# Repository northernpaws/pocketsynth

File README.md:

# Pocket Synth

[Online Board & Schematic View](https://kicanvas.org/?github=https%3A%2F%2Fgithub.com%2Fnorthernpaws%2Fpocketsynth%2Fblob%2Fmain%2Fhardware%2Fdevice%2Fpocket_synth.kicad_pro)

This repository contains my project for an STM32H7-based sequencer, synthesizer, and sampler, all in a small phone-sized pocketable form factor. 

  * 480 MHz Arm® Cortex®-M7 32-bit Processor (`STM32H743ZIT6`)
    * Floating-point unit
    * DSP instructions
    * High-speed memory controller
    * Quad SPI interface for flash
    * High-speed USB host and device mode
    * Several SAI audio blocks
  * 2.4" 240x320 TFT IPS Display (`ER-TFT024IPS-3`)
    * Capacitive touch
  * 24 bit Audio Codec (`NAU88C22YG`)
    * DAC: 94dB SNR and -84dB THD (“A” weighted)
    * ADC: 90dB SNR and -80dB THD (“A” weighted)
    * Integrated BTL speaker driver: 1W into 8Ω
    * Integrated head-phone driver: 40mW into 16Ω
  * Optional Bluetooth Classic and BLE Audio Source (`FSC-BT6038`)
    * Wirelessly connect Bluethooth headphones and speakers
    * Supports various high-fedality audio protocols
    * Note: Audio transmitter does not support other BLE protocols, such as MIDI
  * Optional Wifi and BLE capabilities (`ESP32-C3-MINI-1`)
    * Wifi sample management and transfer
    * BLE MIDI
  * Interal speaker
  * Internal microphone
  * SDRAM for sample pool and audio processing
    * Part allocated to in-memory sample pool for project
    * Part allocated to audio effects processing
    * Variable sizes in similar footprint available, up to 512Mbit:
        * 16bit * 48000Hz = 768,000b/s = 0.768Mb/s
        * 128Mb / 0.768Mb/s = 166.66 seconds of mono audio (`IS42S16800J-7TL`)
        * 256Mb / 0.768Mb/s = 333.33 seconds of mono audio (`IS42S16160J-7TLI`)
        * 512Mb / 0.768Mb/s = 666.66 seconds of mono audio (`IS42S16320F-7TLI`)
  * Micro SD Card
    * Saving and loading projects
      * Transfer and back up projects to a computer
    * Saving and loading samples
      * Load samples from a computer
      * Save samples recorded on the device
  * 3.3v NOR Flash (`MT25QUxxxxxx1xW7` 256M/128M/64M)
    * Stores device settings
    * Small storage space for projects and samples without SD card
    * Provides storage for cross-SD card samples
  * USB-C
    * USB-PD fast charging
    * Possible future audio interface mode
  * MIDI in/out via TRS minijack
  * 16 Multi-Purpose primary keys
    * Hot-swappable Kalih Choc keyswitches (V1 and V2 compatible)
    * RGB LEDs for state indicators
  * Accelerometer and Gyroscope (`LSM6DS3`)
    * Can be used as sequencer parameters
    * Can be recorded for automation inputs
    * Used for auto sleep/wake
  * USB-PD Battery Charge Controller (`MAX77789` or `MAX77757`)
    * 3A fast-charge current
    * 13.4V input voltage
    * Detection for legacy SDP, DCP, and CDP chargers
  * Two-Button Smart Reset (`STM6510`)
    * Hold two input buttons to power off the device if it freezes and power gets latched on

## Step Sequencer

The step sequencer on the device is modeled after popular semantics used by hardware sequencers, such as the Elektron Digitone and Digitakt, OP-1, OP-Z, Pocket Operators, Woovebox, etc.

> The hard requirements of the step sequencer and audio engine are not defined yet because they are under active development.

  * As many projects as the SD card or internal memory can store
    * 128 Patterns (TBD)
      * 8-16 Audio or MIDI tracks per pattern (TBD)
    * 8-24 Songs (arrangements of patterns) (TBD)
  * 8-16 voice polyphony (TBD)
    * 2-3 LFO per voice (TBD)

## Audio

The primary audio engine chain runs at 16bit 44.1Khz, but supports stereo audio effects. 16 bit audio was selected as it had suitable depth without being too large for a small embedded device to reasonably process. 44.1Khz also has a good frequency range, and has been the standard for CDs and many music streaming platforms for a long time.

### Sampling

The sampling engine runs 16bit 44.1Khz and saves and loads samples in single-channel mono.

Samples recoded from the internal or external mic are sampled at 24 bits into the device's SDRAM to provide a decent noise floor, and then filtered and downsampled to 16 bits for saving after they've been edited by the user.

The 16bit @ 44.1Khz sampling parameters provdes a good balance between audio quality, and reasonable utilization of the SDRAM without needing extremely large and expensive SDRAM chips:

```
16bit * 48000Hz = 768,000b/s = 0.768Mb/s
128Mb / 0.768Mb/s = 166.66 seconds of mono audio
256Mb / 0.768Mb/s = 333.33 seconds of mono audio
512Mb / 0.768Mb/s = 666.66 seconds of mono audio
```

> Note that some of the space calculated above (actual amount will be configurable) is allocated to the audio effects processing chain, i.e. for reverb and delay. 

## Attribution

### 3D Models

Majority of 3D models for PCB components are from their respective manufactures, with the exception of:

  - https://grabcad.com/library/kailh-low-profile-mechanical-keyboard-switch-1
  - https://grabcad.com/library/kailh-low-profile-keycaps-1
  - https://cad.grabcad.com/library/sk6812mini-e-led-1

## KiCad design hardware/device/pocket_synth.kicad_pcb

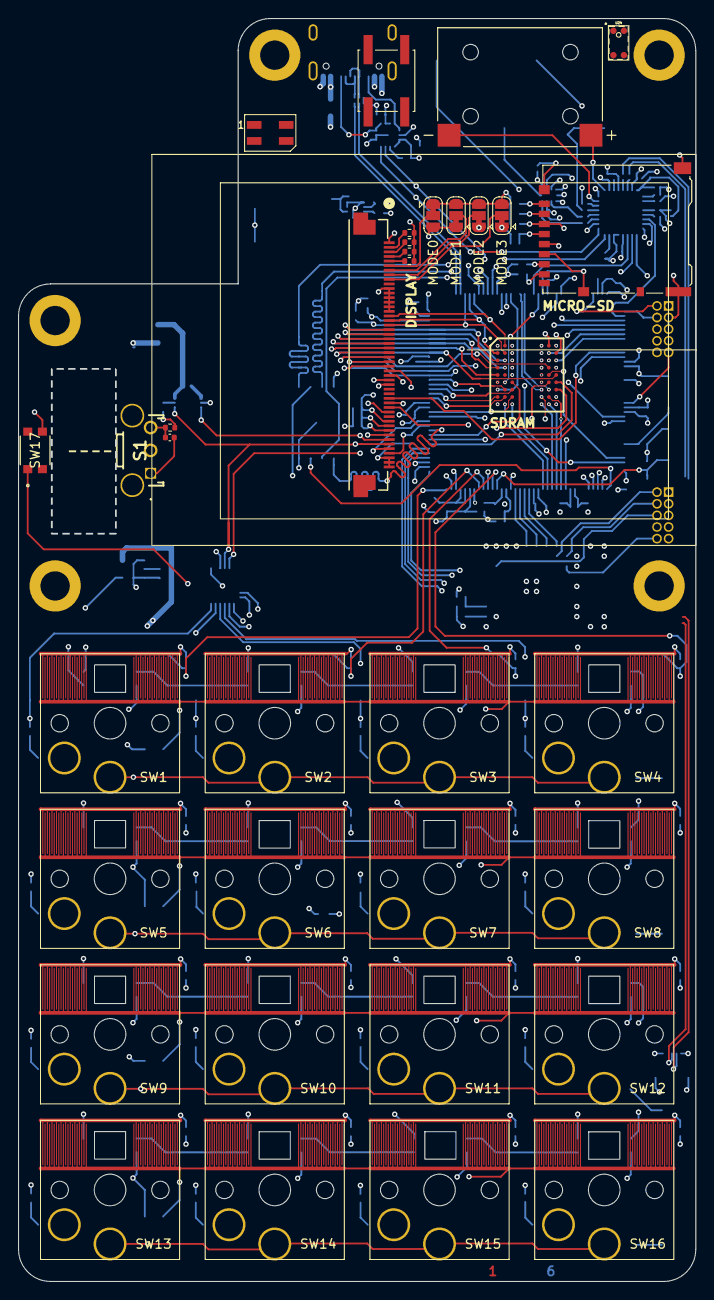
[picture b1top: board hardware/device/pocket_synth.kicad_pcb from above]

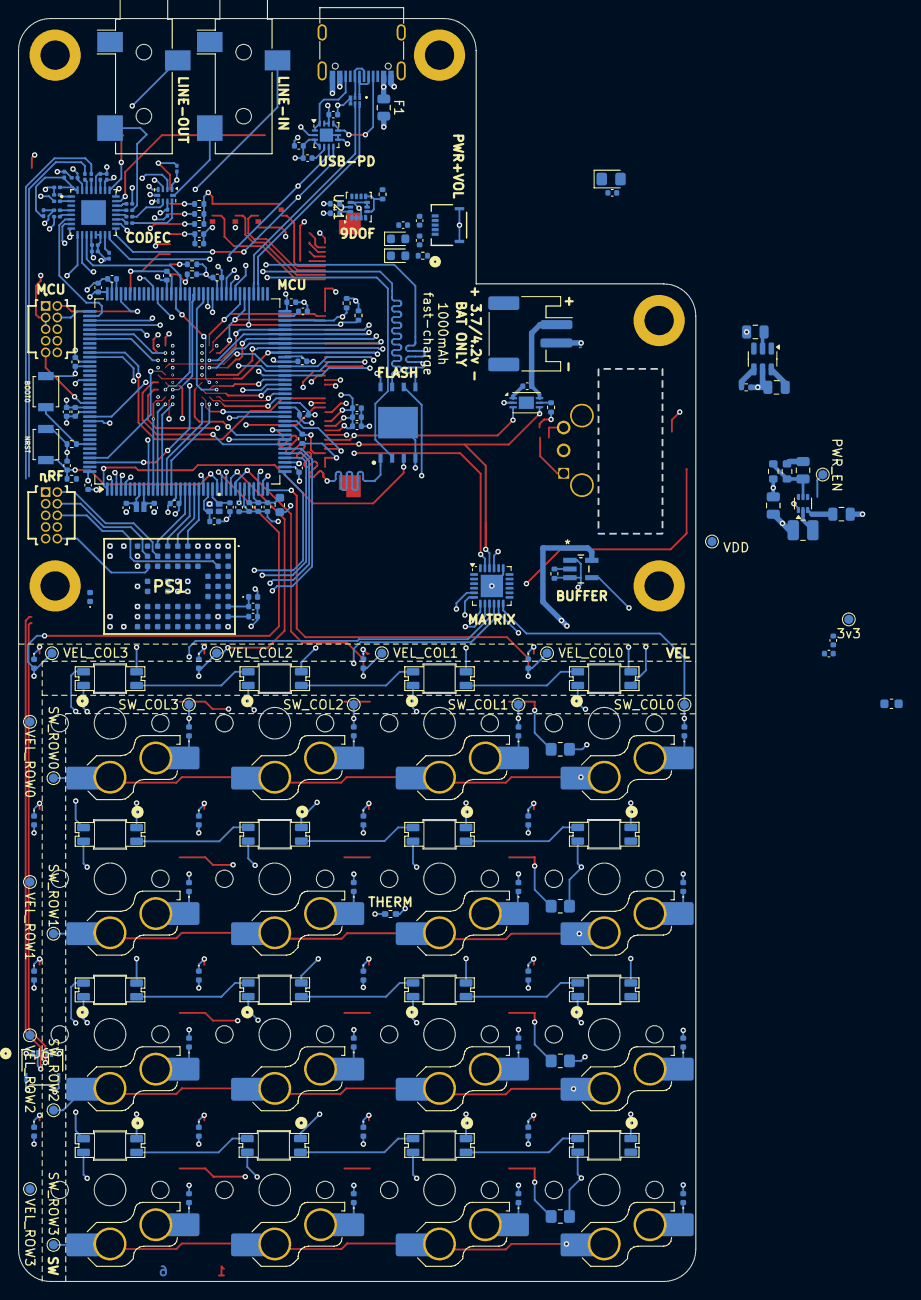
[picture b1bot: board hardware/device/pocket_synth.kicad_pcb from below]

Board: 6 copper layers, 74.0 x 138.0 mm, 231 parts (175 on the bottom side), 221 nets.

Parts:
BT1: Battery; JST_PH_S2B-PH-SM4-TB_1x02-1MP_P2.00mm_Horizontal
C1, C2: 2.2 µF; C_0402_1005Metric
C3: 1 µF; C_0402_1005Metric
C4, C5: 9pF; C_0402_1005Metric
C6, C14: 4.3pF; C_0402_1005Metric
C7: 0.1uF; C_0201_0603Metric
C8, C17, C21, C24: 0.1uF; C_0402_1005Metric
C9: 4.7uF; C_0805_2012Metric
C10, C11: 22uF; C_0402_1005Metric
C12: 22uF; C_0805_2012Metric
C13: 120pF; C_0805_2012Metric
C15, C16: 4.7uF; C_0402_1005Metric
C18: 1uF; C_0402_1005Metric
C19, C20: 1uF; C_0805_2012Metric
C22, C25: 10uF; C_0402_1005Metric
C26: 0.1uF; C_0603_1608Metric
C27, C29, C30, C31, C52, C53: 4.7uF; C_0201_0603Metric
C32, C33, C34, C35, C38, C42, C47, C51: 1uF; C_0201_0603Metric
C36, C37: 220uF; C_0201_0603Metric
C58: 10uf; C_0402_1005Metric
C59, C60, C61, C82, C83, C84, C85, C86, C87, C91, C92: 100nf; C_0402_1005Metric
C81: 0.1uf; C_0402_1005Metric
C88: 10nf; C_0402_1005Metric
C89, C90: 1uf; C_0402_1005Metric
D1, D2, D3, D4, D5, D6, D7, D8, D9, D10, D11, D12, D13, D14, D15, D16, D21, D22, D23, D24, D25, D26, D27, D28, D29, D30, D31, D32, D33, D34, D35, D36, D37, D38: D; D_0402_1005Metric
D17: 3v3_PWR; LED_0805_2012Metric_Pad1.15x1.40mm_HandSolder
D18, D19: D; D_0603_1608Metric
D20: METRONOME; LED_SK6812MINI_PLCC4_3.5x3.5mm_P1.75mm
F1: Fuse; Fuse_0805_2012Metric
FB9: 120r; L_0603_1608Metric
H1, H2, H3, H4, H5: M3; MountingHole_3.2mm_M3_DIN965_Pad
IC1: W25Q512JVEIQ
IC2: IS42S16160J-7BLI
IC3: SP3401-02UTG; SP340102UTG
J1: POT_CONN; CONN_503480-0540_MOL
J2: USB; USB_C_Receptacle_G-Switch_GT-USB-7010ASV
J3: MICRO_SD; microSD_HC_Hirose_DM3AT-SF-PEJM5
J6: HP; CONN_503480-0540_MOL
J8: LINE_OUT; Jack_3.5mm_CUI_SJ-3523-SMT_Horizontal
J9: LINE_IN; Jack_3.5mm_CUI_SJ-3523-SMT_Horizontal
JP1: MODE0; SolderJumper-3_P1.3mm_Bridged12_RoundedPad1.0x1.5mm
JP2: MODE1; SolderJumper-3_P1.3mm_Bridged12_RoundedPad1.0x1.5mm
JP3: MODE2; SolderJumper-3_P1.3mm_Bridged12_RoundedPad1.0x1.5mm
JP4: MODE3; SolderJumper-3_P1.3mm_Bridged12_RoundedPad1.0x1.5mm
L1: 1uH; L_1008_2520Metric
LS1: SPK; AS01808AO-SC18-WP-R
PS1: NORA-B100-00B; NORAB10000B
R2: 70R; C_0402_1005Metric
R3, R11, R13, R14, R15, R16, R17, R22, R35: 10k; R_0402_1005Metric
R4, R5, R6, R7: 6R; R_0402_1005Metric
R8: 100R; R_0402_1005Metric
R9: 222k; R_0201_0603Metric
R10: 10k; R_0201_0603Metric
R12: 100R; C_0402_1005Metric
R19, R25: 2.2k; R_0201_0603Metric
R20: 165R; C_0402_1005Metric
R21: 97.6k; R_0603_1608Metric
R23: 442; R_0603_1608Metric
R24, R26, R27, R64: 0R; R_0402_1005Metric
R28, R30, R31, R32: 10k; R_0805_2012Metric_Pad1.20x1.40mm_HandSolder
R29: 4.7k; C_0402_1005Metric
R33: 100m; C_0402_1005Metric
R34: 1k; R_0402_1005Metric
R36, R37: 4.7k; R_0402_1005Metric
R38: 540R; R_0402_1005Metric
R63: 499k; C_0402_1005Metric
R72: 0R; C_0402_1005Metric
S1: SCROLL_WHEEL; 2416191-1
SW1: TRIG1; SW_Hotswap_Kailh_Choc_V1_1.00u_Pressure
SW2: TRIG2; SW_Hotswap_Kailh_Choc_V1_1.00u_Pressure
SW3: TRIG3; SW_Hotswap_Kailh_Choc_V1_1.00u_Pressure
SW4: TRIG4; SW_Hotswap_Kailh_Choc_V1_1.00u_Pressure
SW5: TRIG5; SW_Hotswap_Kailh_Choc_V1_1.00u_Pressure
SW6: TRIG6; SW_Hotswap_Kailh_Choc_V1_1.00u_Pressure
SW7: TRIG7; SW_Hotswap_Kailh_Choc_V1_1.00u_Pressure
SW8: TRIG8; SW_Hotswap_Kailh_Choc_V1_1.00u_Pressure
SW9: TRIG9; SW_Hotswap_Kailh_Choc_V1_1.00u_Pressure
SW10: TRIG10; SW_Hotswap_Kailh_Choc_V1_1.00u_Pressure
SW11: TRIG11; SW_Hotswap_Kailh_Choc_V1_1.00u_Pressure
SW12: TRIG12; SW_Hotswap_Kailh_Choc_V1_1.00u_Pressure
SW13: TRIG13; SW_Hotswap_Kailh_Choc_V1_1.00u_Pressure
SW14: TRIG14; SW_Hotswap_Kailh_Choc_V1_1.00u_Pressure
SW15: TRIG15; SW_Hotswap_Kailh_Choc_V1_1.00u_Pressure
SW16: TRIG16; SW_Hotswap_Kailh_Choc_V1_1.00u_Pressure
SW17: WHEEL_BTN; KMR221_CNK
SW18: HELP; SW_SPST_EVQQ2
SW24: NRST; SW_SPST_B3U-1000P
SW25: BOOT0; SW_SPST_B3U-1000P
TH1: TH05-3I103FR; R_0402_1005Metric_Pad0.72x0.64mm_HandSolder
TP1: VEL_ROW0; TestPoint_Pad_D1.0mm
TP2: VEL_ROW1; TestPoint_Pad_D1.0mm
TP3: VEL_ROW2; TestPoint_Pad_D1.0mm
TP4: VEL_ROW3; TestPoint_Pad_D1.0mm
TP5: VEL_COL0; TestPoint_Pad_D1.0mm
TP6: VEL_COL1; TestPoint_Pad_D1.0mm
TP7: VEL_COL2; TestPoint_Pad_D1.0mm
TP8: VEL_COL3; TestPoint_Pad_D1.0mm
TP9: SW_COL0; TestPoint_Pad_D1.0mm
TP10: SW_COL1; TestPoint_Pad_D1.0mm
TP11: SW_COL2; TestPoint_Pad_D1.0mm
TP12: SW_COL3; TestPoint_Pad_D1.0mm
TP13: SW_ROW0; TestPoint_Pad_D1.0mm
TP14: 3v3; TestPoint_Pad_D1.0mm
TP15: PWR_EN; TestPoint_Pad_D1.0mm
TP16: SW_ROW1; TestPoint_Pad_D1.0mm
TP17: SW_ROW2; TestPoint_Pad_D1.0mm
TP18: SW_ROW3; TestPoint_Pad_D1.0mm
TP19: VDD; TestPoint_Pad_D1.0mm
U1: BMDU; SAMTEC_FTSH-105-01-F-D-K
U2: TRIG1; SK6812MINI-E
U3: TRIG2; SK6812MINI-E
U4: TRIG3; SK6812MINI-E
U5: TRIG4; SK6812MINI-E
U6: TRIG8; SK6812MINI-E
U7: TRIG7; SK6812MINI-E
U8: TRIG6; SK6812MINI-E
U9: TRIG5; SK6812MINI-E
U10: TRIG9; SK6812MINI-E
U11: TRIG13; SK6812MINI-E
U12: TRIG10; SK6812MINI-E
U13: TRIG14; SK6812MINI-E
U14: TRIG11; SK6812MINI-E
U15: TRIG15; SK6812MINI-E
U16: TRIG12; SK6812MINI-E
U17: TRIG16; SK6812MINI-E
U18: STM32H743ZIT6; LQFP-144_20x20mm_P0.5mm
U19: ER-TFT024IPS-3
U20: TPS62A02DRL; SOT-563
U21: LSM6DS3; LGA-14_3x2.5mm_P0.5mm_LayoutBorder3x4y
U22: nRF; SAMTEC_FTSH-105-01-F-D-K
U23: BQ21040DBV; SOT-23-6
U24: MIC; LMA3722T421-OA5
U25: TCA8418RTWR; WQFN-24-1EP_4x4mm_P0.5mm_EP2.45x2.45mm
U28: TS5A23159RSE; Texas_R-PUQFN-N10
U29: NAU88C22YG
U31: FUSB302B01MPX; WQFN-14-1EP_2.5x2.5mm_P0.5mm_EP1.45x1.45mm
U32: LTC2942; DFN-6-1EP_3x2mm_P0.5mm_EP1.65x1.35mm
U33: SN74AHCT1G125DBVR
Y1: ECS-.327-12.5-1210-TR; XTAL_ECS-.327-12.5-1210-TR
Y4: 8Q-25.000MEEV-T; XTAL_8Q-25.000MEEV-T

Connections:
+3.3V: C7.1, C8.1, C12.1, C13.1, C17.1, C18.1, C21.1, C22.1, C24.1, C25.1, C29.1, C30.1, C31.1, C53.1, C58.1, C59.1, C60.1, C61.1, C82.1, C83.1, C84.1, C85.1, C86.1, C87.1, C90.1, C91.1, C92.1, D17.2 (A), D38.2 (A), FB9.2, IC1.8 (VCC), IC2.A7 (VDDQ), IC2.A9 (VDD), IC2.B3 (VDDQ), IC2.C7 (VDDQ), IC2.D3 (VDDQ), IC2.E7 (VDD), IC2.J9 (VDD), J3.4 (VDD), JP1.1 (A), JP2.3 (B), JP3.3 (B), JP4.3 (B), L1.2, R8.1, R9.1, R12.1, R13.1, R14.1, R15.1, R16.1, R17.1, R23.1, R27.1, R29.1, R34.1, R36.1, R37.1, R63.1, SW25.1, TP14.1, U18.17 (VDD), U18.30 (VDD), U18.39 (VDD), U18.52 (VDD), U18.62 (VDD), U18.72 (VDD), U18.84 (VDD), U18.95 (VDD33_USB), U18.108 (VDD), U18.121 (VDD), U18.131 (VDD), U18.144 (VDD), U19.1 (A), U19.40 (VDDI), U19.41 (VDDI), U19.42 (VCI), U24.2 (VDD), U25.21 (VCC), U28.8 (VCC), U29.13 (VDDC), U29.14 (VDDB), U29.26 (VDDSPK), U29.31 (VDDA), U31.3 (VDD), U31.4 (VDD), U31.12 (VCONN), U31.13 (VCONN)
+3.3VA: C3.1, C88.1, C89.1, FB9.1, U18.32 (VREF+), U18.33 (VDDA)
+BATT: C9.1, C20.1, C26.1, J1.1, R33.1, TP19.1, U2.1 (VDD), U3.1 (VDD), U4.1 (VDD), U5.1 (VDD), U6.1 (VDD), U7.1 (VDD), U8.1 (VDD), U9.1 (VDD), U10.1 (VDD), U11.1 (VDD), U12.1 (VDD), U13.1 (VDD), U14.1 (VDD), U15.1 (VDD), U16.1 (VDD), U17.1 (VDD), U18.6 (VBAT), U20.3 (VIN), U23.2 (OUT), U32.1 (SENSE+), U33.5 (VCC)
/Audio/AUX_L: C38.1, U28.9
/Audio/AUX_R: C42.1, U28.7
/Audio/CODEC.ADCDAT: U18.2 (SAI1_SD_B), U29.9 (ADCOUT)
/Audio/CODEC.BCLK: U18.4 (SAI1_SCK_A), U29.8 (BCLK)
/Audio/CODEC.DACDAT: U18.5 (SAI1_SD_A), U29.10 (DACIN)
/Audio/CODEC.LRCLK: U18.3 (SAI1_FS_A), U29.7 (FS)
/Audio/CODEC.MCLK: U18.92 (SAI1_MCLK_A), U29.11 (MCLK)
/Audio/CODEC_IRQ: U18.110 (PA15), U29.6 (RLIN/GPIO3)
/Audio/JACK_DET: J6.1, R9.2, U29.15 (CSB/GPIO1)
/Audio/MIC_L: C32.1, R19.1, U28.2
/Audio/MIC_OUT: U24.1 (OUT), U29.3 (LLIN/GPIO2)
/Audio/MIC_R: C47.1, R25.1, U28.4
/Audio/MIC_SELECT: R10.1, U18.98 (PC8), U28.1, U28.5
/Display/FMC.A0: IC2.H7 (A0), U18.10 (FMC_A0), U19.37 (DCx)
/Display/FMC.A1: IC2.H8 (A1), U18.11 (FMC_A1)
/Display/FMC.A2: IC2.J8 (A2), U18.12 (FMC_A2)
/Display/FMC.A3: IC2.J7 (A3), U18.13 (FMC_A3)
/Display/FMC.A4: IC2.J3 (A4), U18.14 (FMC_A4)
/Display/FMC.A5: IC2.J2 (A5), U18.15 (FMC_A5)
/Display/FMC.A6: IC2.H3 (A6), U18.50 (FMC_A6)
/Display/FMC.A7: IC2.H2 (A7), U18.53 (FMC_A7)
/Display/FMC.A8: IC2.H1 (A8), U18.54 (FMC_A8)
/Display/FMC.A9: IC2.G3 (A9), U18.55 (FMC_A9)
/Display/FMC.A10: IC2.H9 (A10), U18.56 (FMC_A10)
/Display/FMC.A11: IC2.G2 (A11), U18.57 (FMC_A11)
/Display/FMC.A12: IC2.G1 (A12), U18.87 (FMC_A12)
/Display/FMC.BA0: IC2.G7 (BA0), U18.89 (FMC_BA0)
/Display/FMC.BA1: IC2.G8 (BA1), U18.90 (FMC_BA1)
/Display/FMC.CAS: IC2.F7 (~CAS), U18.132 (FMC_SDNCAS)
/Display/FMC.CKE: IC2.F3 (CKE), U18.45 (FMC_SDCKE0)
/Display/FMC.CLK: IC2.F2 (CLK), U18.93 (FMC_SDCLK)
/Display/FMC.D0: IC2.A8 (DQ0), U18.85 (FMC_D0), U19.32 (D0)
/Display/FMC.D1: IC2.B9 (DQ1), U18.86 (FMC_D1), U19.31 (D1)
/Display/FMC.D2: IC2.B8 (DQ2), U18.114 (FMC_D2), U19.30 (D2)
/Display/FMC.D3: IC2.C9 (DQ3), U18.115 (FMC_D3), U19.29 (D3)
/Display/FMC.D4: IC2.C8 (DQ4), U18.58 (FMC_D4), U19.28 (D4)
/Display/FMC.D5: IC2.D9 (DQ5), U18.59 (FMC_D5), U19.27 (D5)
/Display/FMC.D6: IC2.D8 (DQ6), U18.60 (FMC_D6), U19.26 (D6)
/Display/FMC.D7: IC2.E9 (DQ7), U18.63 (FMC_D7), U19.25 (D7)
/Display/FMC.D8: IC2.E1 (DQ8), U18.64 (FMC_D8), U19.24 (D8)
/Display/FMC.D9: IC2.D2 (DQ9), U18.65 (FMC_D9), U19.23 (D9)
/Display/FMC.D10: IC2.D1 (DQ10), U18.66 (FMC_D10), U19.22 (D10)
/Display/FMC.D11: IC2.C2 (DQ11), U18.67 (FMC_D11), U19.21 (D11)
/Display/FMC.D12: IC2.C1 (DQ12), U18.68 (FMC_D12), U19.20 (D12)
/Display/FMC.D13: IC2.B2 (DQ13), U18.77 (FMC_D13), U19.19 (D13)
/Display/FMC.D14: IC2.B1 (DQ14), U18.78 (FMC_D14), U19.18 (D14)
/Display/FMC.D15: IC2.A2 (DQ15), U18.79 (FMC_D15), U19.17 (D15)
/Display/FMC.DQMH: IC2.F1 (DQMH), U18.142 (FMC_NBL1)
/Display/FMC.DQML: IC2.E8 (DQML), U18.141 (FMC_NBL0)
/Display/FMC.NE0: IC2.G9 (~CS), U18.44 (FMC_SDNE0)
/Display/FMC.NE1: U18.97 (FMC_NE1), U19.38 (CSx)
/Display/FMC.NOE: U18.118 (FMC_NOE), U19.35 (RDx)
/Display/FMC.NWE: U18.119 (FMC_NWE), U19.36 (WRx)
/Display/FMC.RAS: IC2.F8 (~RAS), U18.49 (FMC_SDNRAS)
/Display/FMC.WE: IC2.F9 (~WE), U18.43 (FMC_SDNWE)
/Display/MODE0: JP1.2 (C), U19.6 (MODE0)
/Display/MODE1: JP2.2 (C), U19.7 (MODE1)
/Display/MODE2: JP3.2 (C), U19.8 (MODE2)
/Display/MODE3: JP4.2 (C), U19.9 (MODE3)
/Display/TOUCH_INT: U18.48 (PB2), U19.46 (INT)
/Display/TOUCH_RST: R11.1, U18.47 (PB1), U19.47 (RESET)
/I2C.SCL: R26.1, R37.2, U18.69 (I2C2_SCL), U19.44 (SCL), U25.23 (SCL), U29.16 (SCLK), U31.6 (SCL), U32.3 (SCL)
/I2C.SDA: R24.1, R36.2, U18.70 (I2C2_SDA), U19.45 (SDA), U25.22 (SDA), U29.17 (SDIO), U31.7 (SDA), U32.4 (SDA)
/Keypad/COL0: D22.2 (A), D26.2 (A), D30.2 (A), D34.2 (A), TP5.1, U18.36 (PA2)
/Keypad/COL1: D23.2 (A), D27.2 (A), D31.2 (A), D35.2 (A), TP6.1, U18.29 (PC3_C)
/Keypad/COL2: D24.2 (A), D28.2 (A), D32.2 (A), D36.2 (A), TP7.1, U18.28 (PC2_C)
/Keypad/COL3: D25.2 (A), D29.2 (A), D33.2 (A), D37.2 (A), TP8.1, U18.26 (PC0)
/Keypad/ROW0: R28.2, SW1.3, SW2.3, SW3.3, SW4.3, TP1.1, U18.37 (PA3)
/Keypad/ROW1: R30.2, SW5.3, SW6.3, SW7.3, SW8.3, TP2.1, U18.40 (PA4)
/Keypad/ROW2: R31.2, SW9.3, SW10.3, SW11.3, SW12.3, TP3.1, U18.41 (PA5)
/Keypad/ROW3: R32.2, SW13.3, SW14.3, SW15.3, SW16.3, TP4.1, U18.42 (PA6)
/Keypad/SW_COL0: D1.2 (A), D5.2 (A), D9.2 (A), D13.2 (A), TP9.1, U25.12 (COL3)
/Keypad/SW_COL1: D2.2 (A), D6.2 (A), D10.2 (A), D14.2 (A), TP10.1, U25.11 (COL2)
/Keypad/SW_COL2: D3.2 (A), D7.2 (A), D11.2 (A), D15.2 (A), TP11.1, U25.10 (COL1)
/Keypad/SW_COL3: D4.2 (A), D8.2 (A), D12.2 (A), D16.2 (A), TP12.1, U25.9 (COL0)
/Keypad/SW_ROW0: SW1.1, SW2.1, SW3.1, SW4.1, TP13.1, U25.5 (ROW3)
/Keypad/SW_ROW1: SW5.1, SW6.1, SW7.1, SW8.1, TP16.1, U25.6 (ROW2)
/Keypad/SW_ROW2: SW9.1, SW10.1, SW11.1, SW12.1, TP17.1, U25.7 (ROW1)
/Keypad/SW_ROW3: SW13.1, SW14.1, SW15.1, SW16.1, TP18.1, U25.8 (ROW0)
/Keypad/WHEEL_BTN: SW17.1, U25.3 (ROW5)
/Lighting/LED_DIN: R35.1, U33.2 (A)
/MCU/AUDIO_UART.RX: PS1.B1 (P0.08/TRACEDATA3/SCK), U18.35 (UART4_RX)
/MCU/AUDIO_UART.TX: PS1.C1 (P0.10/TRACEDATA1/MISO), U18.34 (UART4_TX)
/MCU/BOOT0: R22.1, SW25.2, U18.138 (BOOT0)
/MCU/DEBUG_RX: U1.7 (UART_TX), U18.124 (USART6_RX)
/MCU/DEBUG_TX: U1.9 (UART_RX), U18.129 (USART6_TX)
/MCU/EXP_CODEC.ADCDAT: PS1.D1 (P0.15/IO2), U18.27 (SAI4_SD_A)
/MCU/EXP_CODEC.BCLK: PS1.F1 (P0.17/SCK), U18.20 (SAI4_SCK_B)
/MCU/EXP_CODEC.DACDAT: PS1.H1 (P0.24), U18.18 (SAI4_SD_B)
/MCU/EXP_CODEC.LRCLK: PS1.E1 (P0.18/CSN), U18.21 (SAI4_FS_B)
/MCU/EXP_CODEC.MCLK: PS1.G1 (P1.06), U18.19 (SAI4_MCLK_B)
/MCU/FLASH_CS: IC1.1 (~CS), U18.46 (PB0)
/MCU/HSE_OSC_IN: C4.2, U18.23 (RCC_OSC_IN), Y4.3
/MCU/HSE_OSC_OUT: C5.2, U18.24 (RCC_OSC_OUT), Y4.1
/MCU/LSE_OSC_IN: C6.2, U18.8 (RCC_OSC32_IN), Y1.2
/MCU/LSE_OSC_OUT: C14.2, U18.9 (RCC_OSC32_OUT), Y1.1
/MCU/QSPI.CLK: IC1.6 (CLK), U18.22 (QUADSPI_CLK)
/MCU/QSPI.IO0: IC1.5 (DI_(IO0)), U18.80 (QUADSPI_BK1_IO0)
/MCU/QSPI.IO1: IC1.2 (DO_(IO1)), U18.81 (QUADSPI_BK1_IO1)
/MCU/QSPI.IO2: IC1.3 (~WP_(IO2)), U18.1 (QUADSPI_BK1_IO2)
/MCU/QSPI.IO3: IC1.7 (~RESET_(IO3)), U18.82 (QUADSPI_BK1_IO3)
/MCU/SPI.CLK: J3.5 (CLK), U18.111 (SPI3_SCK)
/MCU/SPI.PICO: J3.3 (CMD), R13.2, U18.113 (SPI3_MOSI)
/MCU/SPI.POCI: J3.7 (DAT0), R14.2, U18.112 (SPI3_MISO)
/MCU/SWD_RESET: C81.2, R64.2, SW24.2, U1.10 (nRST), U18.25 (NRST)
/MCU/SWD_SWCLK: U1.4 (SWDCLK), U18.109 (DEBUG_JTCK-SWCLK)
/MCU/SWD_SWDIO: U1.2 (SWDIO), U18.105 (DEBUG_JTMS-SWDIO)
/MCU/SWD_SWO: U1.6 (SWO), U18.133 (DEBUG_JTDO-SWO)
/MCU/USB_INT: R29.2, U31.5 (INT_N)
/MCU/~MCU_PWR_EN: D19.2 (A), R3.1
/Memory/SD_CS: J3.2 (DAT3/CD), R17.2
/Power/3v3_PG: R63.2, R64.1, R72.1, R72.2, U20.6 (PG)
/Power/FUEL_INT: R34.2, U32.5 (~AL/CC)
/Power/USB_D+: IC3.2 (I/O2), IC3.5 (NC_1), J2.A6 (D+), J2.B6 (D+), U18.76 (USB_OTG_HS_DP)
/Power/USB_D-: IC3.1 (I/O1), IC3.6 (NC_2), J2.A7 (D-), J2.B7 (D-), U18.75 (USB_OTG_HS_DM)
/Power/VOL_A: C11.1, J1.3, R12.2
/Power/VOL_C: C11.2, J1.5
/Power/~PWR_EN: D18.1 (K), D19.1 (K), TP15.1, U20.4 (EN)
/RF/SWO: PS1.B3 (P0.11/TRACEDATA0/CSN), U22.6 (SWO)
CASE: H1.1, H2.1, H3.1, H4.1, H5.1
GND: BT1.2 (-), C1.2, C2.2, C3.2, C4.1, C5.1, C6.1, C7.2, C8.2, C9.2, C12.2, C14.1, C15.2, C16.2, C17.2, C18.2, C19.2, C20.2, C21.2, C22.2, C24.2, C25.2, C26.2, C27.2, C29.2, C30.2, C31.2, C33.1, C51.1, C52.2, C53.2, C58.2, C59.2, C60.2, C61.2, C81.1, C82.2, C83.2, C84.2, C85.2, C86.2, C87.2, C88.2, C89.2, C90.2, C91.2, C92.2, IC1.4 (GND), IC1.9 (EP), IC2.A1 (VSS), IC2.A3 (VSSQ), IC2.B7 (VSSQ), IC2.C3 (VSSQ), IC2.D7 (VSSQ), IC2.E3 (VSS), IC2.J1 (VSS), IC3.3 (GND), IC3.4 (GND), J1.6 (MP), J1.7 (MP), J2.A1 (GND), J2.A12 (GND), J2.B1 (GND), J2.B12 (GND), J2.S1 (SHIELD), J3.6 (VSS), J3.11 (SHIELD), J6.5, J6.6 (MP), J6.7 (MP), J8.S, J9.S, JP1.3 (B), JP2.1 (A), JP3.1 (A), JP4.1 (A), PS1.A1 (VSS), PS1.A9 (VSS_2), PS1.B2 (VSS_3), PS1.B8 (VSS_4), PS1.E4 (VSS_5), PS1.E5 (VSS_6), PS1.F4 (VSS_7), PS1.F5 (VSS_8), PS1.K2 (VSS_9), PS1.K3 (VSS_10), PS1.K5 (VSS_11), PS1.K7 (VSS_12), PS1.K8 (VSS_13), PS1.L1 (VSS_14), PS1.L9 (VSS_15), PS1.M1 (VSS_16), PS1.M2 (VSS_17), PS1.M8 (VSS_18), PS1.M9 (VSS_19), R2.2, R3.2, R4.1, R5.1, R6.1, R7.1, R10.2, R11.2, R21.2, R22.2, R28.1, R30.1, R31.1, R32.1, R35.2, R38.2, S1.4 (MH1), S1.5 (MH2), SW17.3, SW24.1, TH1.2, U1.3 (GND), U1.5 (GND), U2.3 (GND), U3.3 (GND), U4.3 (GND), U5.3 (GND), U6.3 (GND), U7.3 (GND), U8.3 (GND), U9.3 (GND), U10.3 (GND), U11.3 (GND), U12.3 (GND), U13.3 (GND), U14.3 (GND), U15.3 (GND), U16.3 (GND), U17.3 (GND), U18.16 (VSS), U18.31 (VSSA), U18.38 (VSS), U18.51 (VSS), U18.61 (VSS), U18.83 (VSS), U18.94 (VSS), U18.107 (VSS), U18.120 (VSS), U18.130 (VSS), U19.11 (VSYNC), U19.12 (HSYNC), U19.13 (DOTCLK), U19.14 (DE), U19.15 (D17), U19.16 (D16), U19.43 (GND), U19.48 (GND), U19.49 (GND), U19.50 (GND), U20.1 (GND), U21.1 (SDO/SA0), U21.2 (SDX), U21.3 (SCX), U21.6 (GND), U21.7 (GND), U21.12 (CS), U22.3 (GND), U22.5 (GND), U23.5 (GND), U24.3 (GND), U24.4 (GND), U25.19 (GND), U25.25 (EP), U28.3 (GND), U29.12 (VSSD), U29.18 (MODE), U29.24 (VSSSPK), U29.28 (VSSA), U31.8 (GND), U31.9 (GND), U31.15 (GND), U32.2 (GND), U33.1 (*OE), U33.3 (GND), Y4.2
unnamed: BT1.1 (+), R33.2, U32.6 (SENSE-)
unnamed: C1.1, U18.106 (VCAP)
unnamed: C2.1, U18.71 (VCAP)
unnamed: C34.2, J8.T
unnamed: C35.2, J8.R
unnamed: C36.2, J6.2
unnamed: C37.2, J6.3
unnamed: D1.1 (K), SW1.2
unnamed: D2.1 (K), SW2.2
unnamed: D3.1 (K), SW3.2
unnamed: D4.1 (K), SW4.2
unnamed: D5.1 (K), SW5.2
unnamed: D6.1 (K), SW6.2
unnamed: D7.1 (K), SW7.2
unnamed: D8.1 (K), SW8.2
unnamed: D9.1 (K), SW9.2
unnamed: D10.1 (K), SW10.2
unnamed: D11.1 (K), SW11.2
unnamed: D12.1 (K), SW12.2
unnamed: D13.1 (K), SW13.2
unnamed: D14.1 (K), SW14.2
unnamed: D15.1 (K), SW15.2
unnamed: D16.1 (K), SW16.2
unnamed: D17.1 (K), R2.1
unnamed: D18.2 (A), J1.2, R20.1
unnamed: D21.2 (A), U22.1 (vRef)
unnamed: C15.1, C16.1, D21.1 (K), D38.1 (K), PS1.A7 (VDD), PS1.A8 (VDDH), PS1.B7 (VDD_2)
unnamed: D22.1 (K), SW1.4
unnamed: D23.1 (K), SW2.4
unnamed: D24.1 (K), SW3.4
unnamed: D25.1 (K), SW4.4
unnamed: D26.1 (K), SW5.4
unnamed: D27.1 (K), SW6.4
unnamed: D28.1 (K), SW7.4
unnamed: D29.1 (K), SW8.4
unnamed: D30.1 (K), SW9.4
unnamed: D31.1 (K), SW10.4
unnamed: D32.1 (K), SW11.4
unnamed: D33.1 (K), SW12.4
unnamed: D34.1 (K), SW13.4
unnamed: D35.1 (K), SW14.4
unnamed: D36.1 (K), SW15.4
unnamed: D37.1 (K), SW16.4
unnamed: F1.1, J2.A4 (VBUS), J2.A9 (VBUS), J2.B4 (VBUS), J2.B9 (VBUS)
unnamed: J2.A5 (CC1), U31.10 (CC1), U31.11 (CC1)
unnamed: J2.B5 (CC2), U31.1 (CC2), U31.14 (CC2)
unnamed: J3.8 (DAT1), R15.2
unnamed: J3.1 (DAT2), R16.2
unnamed: J9.R, U28.6
unnamed: J9.T, U28.10
unnamed: PS1.J2 (SWDCLK), U22.4 (SWDCLK)
unnamed: PS1.H2 (SWDIO), U22.2 (SWDIO)
unnamed: PS1.J3 (~RESET), U22.10 (nRST)
unnamed: C10.2, S1.1 (A)
unnamed: C10.1, R8.2, S1.3 (B)
unnamed: U2.4 (DIN), U33.4 (Y)
unnamed: U2.2 (DOUT), U3.4 (DIN)
unnamed: U3.2 (DOUT), U4.4 (DIN)
unnamed: U4.2 (DOUT), U5.4 (DIN)
unnamed: U5.2 (DOUT), U6.4 (DIN)
unnamed: U6.2 (DOUT), U7.4 (DIN)
unnamed: U7.2 (DOUT), U8.4 (DIN)
unnamed: U8.2 (DOUT), U9.4 (DIN)
unnamed: U9.2 (DOUT), U10.4 (DIN)
unnamed: U10.2 (DOUT), U12.4 (DIN)
unnamed: U11.4 (DIN), U13.2 (DOUT)
unnamed: U12.2 (DOUT), U14.4 (DIN)
unnamed: U13.4 (DIN), U15.2 (DOUT)
unnamed: U14.2 (DOUT), U16.4 (DIN)
unnamed: U15.4 (DIN), U17.2 (DOUT)
unnamed: U16.2 (DOUT), U17.4 (DIN)
unnamed: R4.2, U19.2 (K1)
unnamed: R5.2, U19.3 (K2)
unnamed: R6.2, U19.4 (K3)
unnamed: R7.2, U19.5 (K4)
unnamed: C13.2, R21.1, R23.2, U20.5 (FB)
unnamed: L1.1, U20.2 (SW)
unnamed: R26.2, U21.13 (SCL)
unnamed: R24.2, U21.14 (SDA)
unnamed: R27.2, U21.5 (VDDIO), U21.8 (VDD)
unnamed: R38.1, U23.4 (ISET)
unnamed: TH1.1, U23.1 (TS)
unnamed: C34.1, U29.21 (AUXOUT1)
unnamed: C35.1, U29.22 (AUXOUT2)
unnamed: C38.2, U29.19 (LAUXIN)
unnamed: C36.1, U29.30 (LHP)
unnamed: C33.2, U29.2 (LMICN)
unnamed: C32.2, U29.1 (LMICP)
unnamed: LS1.P, U29.25 (LSPKOUT)
unnamed: C52.1, R19.2, R25.2, U29.32 (MICBIAS)
unnamed: C42.2, U29.20 (RAUXIN)
unnamed: C37.1, U29.29 (RHP)
unnamed: C51.2, U29.5 (RMICN)
unnamed: C47.2, U29.4 (RMICP)
unnamed: LS1.N, U29.23 (RSPKOUT)
unnamed: C27.1, U29.27 (VREF)
VBUS: C19.1, F1.2, U23.6 (VIN), U31.2 (VBUS)

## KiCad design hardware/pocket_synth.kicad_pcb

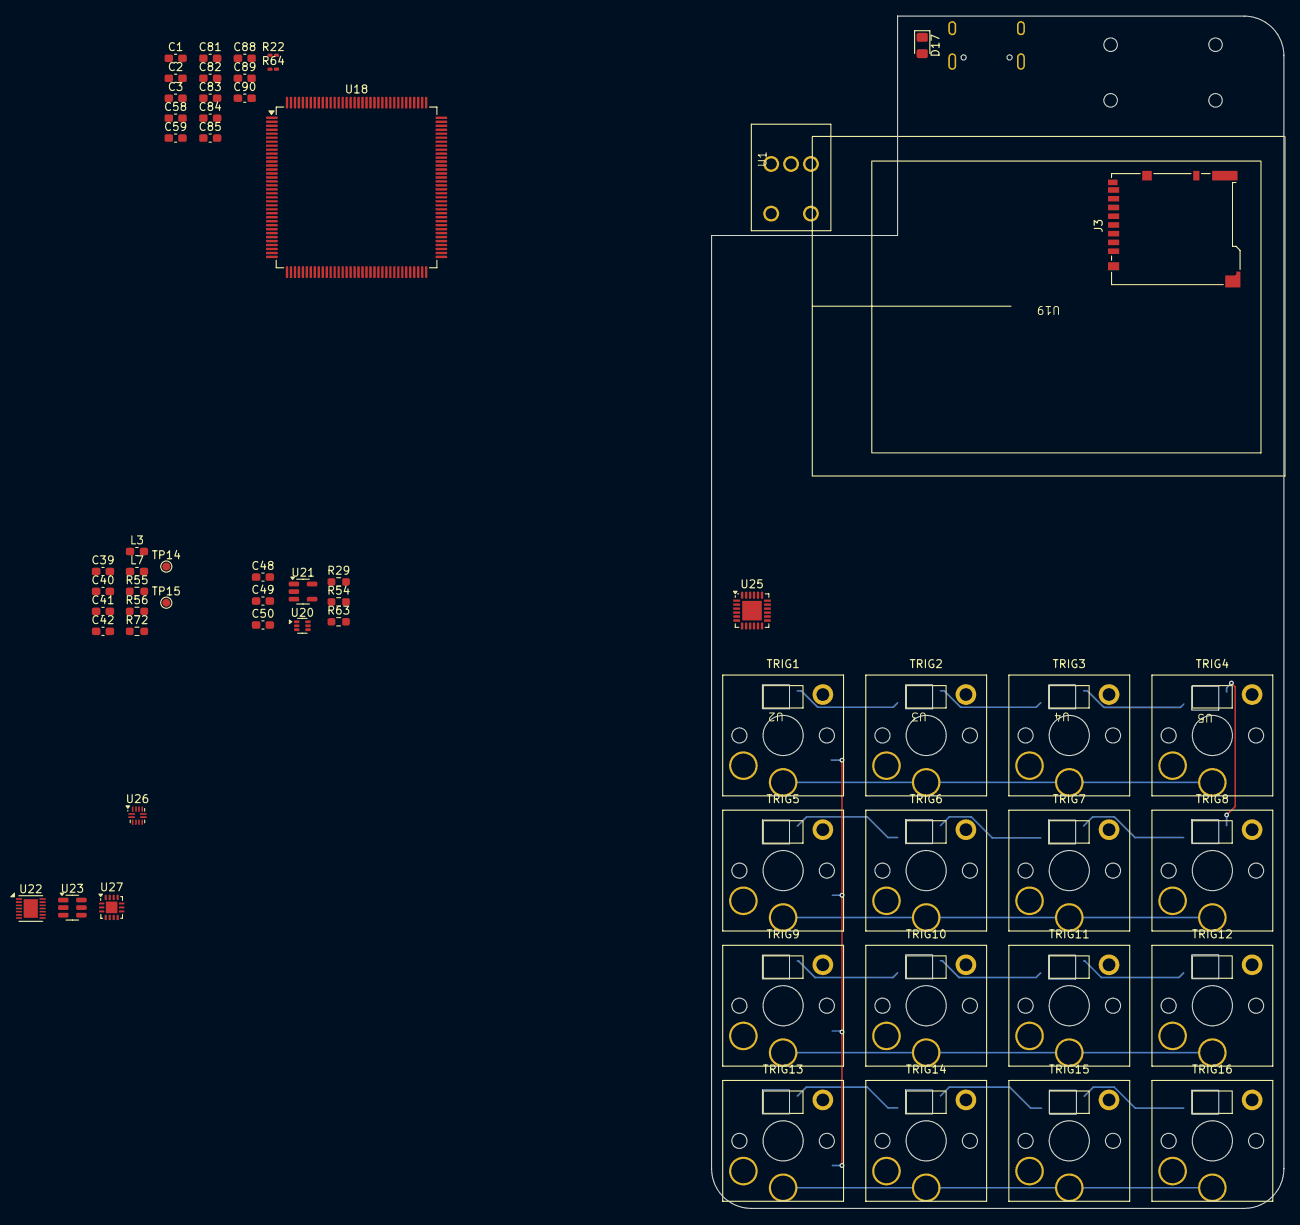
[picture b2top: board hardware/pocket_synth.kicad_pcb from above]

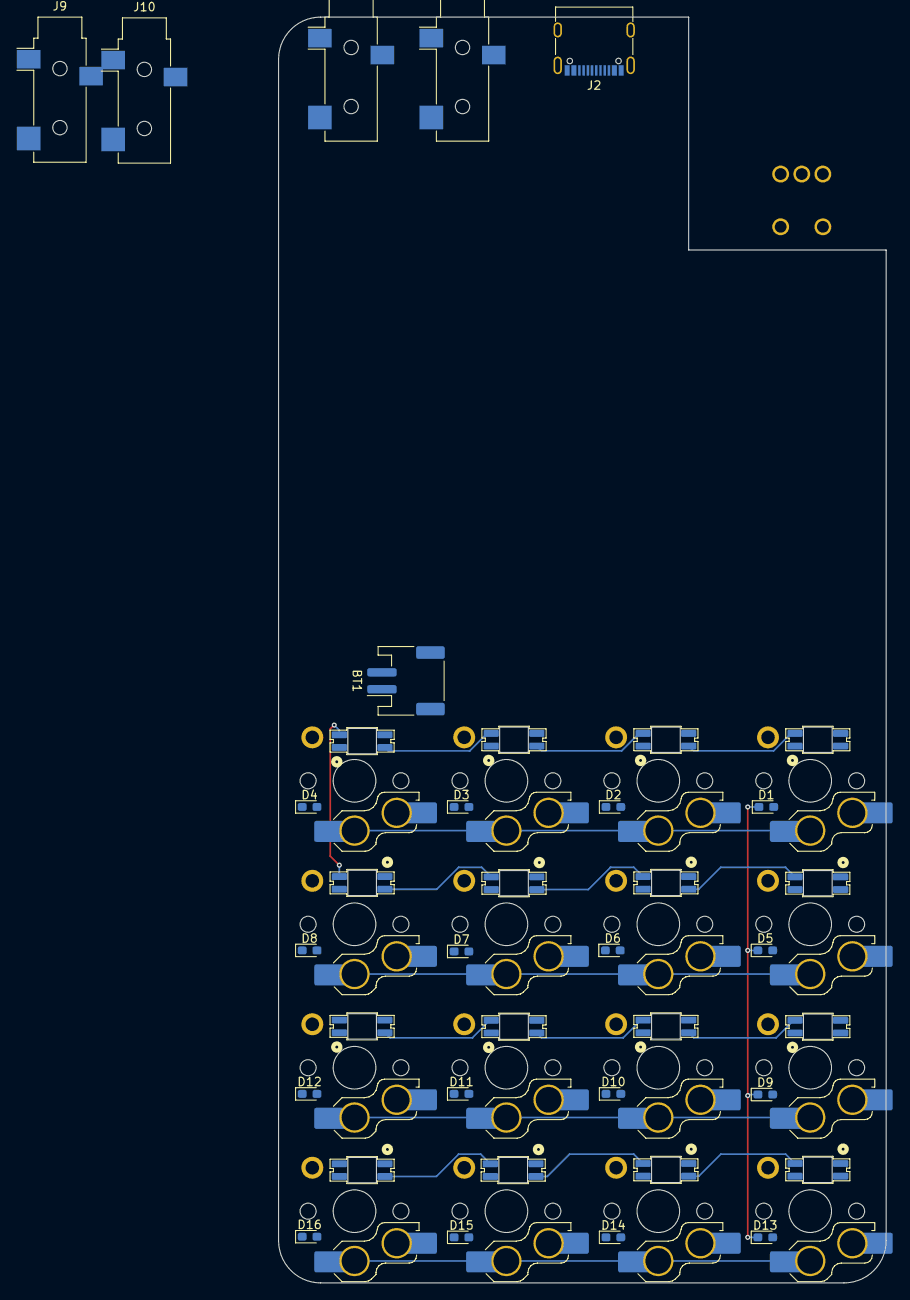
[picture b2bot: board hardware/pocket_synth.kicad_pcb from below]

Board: 4 copper layers, 72.0 x 150.0 mm, 98 parts (22 on the bottom side), 60 nets.

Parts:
BT1: Battery; JST_PH_S2B-PH-SM4-TB_1x02-1MP_P2.00mm_Horizontal
C1, C2: 2.2 µF; C_0603_1608Metric_Pad1.08x0.95mm_HandSolder
C3: 1 µF; C_0603_1608Metric_Pad1.08x0.95mm_HandSolder
C39, C41, C42, C58: 10uf; C_0603_1608Metric_Pad1.08x0.95mm_HandSolder
C40, C81: 0.1uf; C_0603_1608Metric_Pad1.08x0.95mm_HandSolder
C48: 120pF; C_0603_1608Metric_Pad1.08x0.95mm_HandSolder
C49: 22uf; C_0603_1608Metric_Pad1.08x0.95mm_HandSolder
C50: 4.7uf; C_0603_1608Metric_Pad1.08x0.95mm_HandSolder
C59, C82, C83, C84, C85: 100nf; C_0603_1608Metric_Pad1.08x0.95mm_HandSolder
C88: 10nf; C_0603_1608Metric_Pad1.08x0.95mm_HandSolder
C89, C90: 1uf; C_0603_1608Metric_Pad1.08x0.95mm_HandSolder
D1, D2, D3, D4, D5, D6, D7, D8, D9, D10, D11, D12, D13, D14, D15, D16: D; D_0603_1608Metric_Pad1.05x0.95mm_HandSolder
D17: PWR; LED_0805_2012Metric_Pad1.15x1.40mm_HandSolder
J2: USB; USB_C_Receptacle_G-Switch_GT-USB-7010ASV
J3: Micro_SD_Card_Det_Hirose_DM3AT; microSD_HC_Hirose_DM3BT-DSF-PEJS
J6: LINE_IN; Jack_3.5mm_CUI_SJ-3523-SMT_Horizontal
J8: LINE_OUT; Jack_3.5mm_CUI_SJ-3523-SMT_Horizontal
J9: MIDI_IN; Jack_3.5mm_CUI_SJ-3523-SMT_Horizontal
J10: MIDI_OUT; Jack_3.5mm_CUI_SJ-3523-SMT_Horizontal
L3: 10uh; L_0603_1608Metric_Pad1.05x0.95mm_HandSolder
L7: 1uh; L_0603_1608Metric_Pad1.05x0.95mm_HandSolder
R22: 10k; R_0201_0603Metric_Pad0.64x0.40mm_HandSolder
R29: 442k; R_0603_1608Metric_Pad0.98x0.95mm_HandSolder
R54: 97.6k; R_0603_1608Metric_Pad0.98x0.95mm_HandSolder
R55: 24.9k; R_0603_1608Metric_Pad0.98x0.95mm_HandSolder
R56: 20.0k; R_0603_1608Metric_Pad0.98x0.95mm_HandSolder
R63: 499k; R_0603_1608Metric_Pad0.98x0.95mm_HandSolder
R64: 0R; R_0201_0603Metric_Pad0.64x0.40mm_HandSolder
R72: 0R; R_0603_1608Metric_Pad0.98x0.95mm_HandSolder
SW1: TRIG1; SW_Hotswap_Kailh_Choc_V1V2_Plated_1.00u
SW2: TRIG2; SW_Hotswap_Kailh_Choc_V1V2_Plated_1.00u
SW3: TRIG3; SW_Hotswap_Kailh_Choc_V1V2_Plated_1.00u
SW4: TRIG4; SW_Hotswap_Kailh_Choc_V1V2_Plated_1.00u
SW5: TRIG5; SW_Hotswap_Kailh_Choc_V1V2_Plated_1.00u
SW6: TRIG6; SW_Hotswap_Kailh_Choc_V1V2_Plated_1.00u
SW7: TRIG7; SW_Hotswap_Kailh_Choc_V1V2_Plated_1.00u
SW8: TRIG8; SW_Hotswap_Kailh_Choc_V1V2_Plated_1.00u
SW9: TRIG9; SW_Hotswap_Kailh_Choc_V1V2_Plated_1.00u
SW10: TRIG10; SW_Hotswap_Kailh_Choc_V1V2_Plated_1.00u
SW11: TRIG11; SW_Hotswap_Kailh_Choc_V1V2_Plated_1.00u
SW12: TRIG12; SW_Hotswap_Kailh_Choc_V1V2_Plated_1.00u
SW13: TRIG13; SW_Hotswap_Kailh_Choc_V1V2_Plated_1.00u
SW14: TRIG14; SW_Hotswap_Kailh_Choc_V1V2_Plated_1.00u
SW15: TRIG15; SW_Hotswap_Kailh_Choc_V1V2_Plated_1.00u
SW16: TRIG16; SW_Hotswap_Kailh_Choc_V1V2_Plated_1.00u
TP14: 3v3; TestPoint_Pad_D1.0mm
TP15: 1v8; TestPoint_Pad_D1.0mm
U1: VOL_PWR_POT; PTR901-2015K-B103
U2: TRIG1; SK6812MINI-E
U3: TRIG2; SK6812MINI-E
U4: TRIG3; SK6812MINI-E
U5: TRIG4; SK6812MINI-E
U6: TRIG8; SK6812MINI-E
U7: TRIG7; SK6812MINI-E
U8: TRIG6; SK6812MINI-E
U9: TRIG5; SK6812MINI-E
U10: TRIG9; SK6812MINI-E
U11: TRIG13; SK6812MINI-E
U12: TRIG10; SK6812MINI-E
U13: TRIG14; SK6812MINI-E
U14: TRIG11; SK6812MINI-E
U15: TRIG15; SK6812MINI-E
U16: TRIG12; SK6812MINI-E
U17: TRIG16; SK6812MINI-E
U18: STM32H743ZIT6; LQFP-144_20x20mm_P0.5mm
U19: ER-TFT024IPS-3
U20: TPS62A02DRL; SOT-563
U21: TPS560200; SOT-23-5
U22: MAX17261xxTD; TDFN-14-1EP_3x3mm_P0.4mm_EP1.78x2.35mm
U23: BQ21040DBV; SOT-23-6
U25: TCA8418RTWR; WQFN-24-1EP_4x4mm_P0.5mm_EP2.45x2.45mm
U26: FUSB303BTMX; Texas_X2QFN-12_1.6x1.6mm_P0.4mm
U27: FUSB302B01MPX; WQFN-14-1EP_2.5x2.5mm_P0.5mm_EP1.45x1.45mm

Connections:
+1V8: C41.1, C42.1, L3.2, R55.1, TP15.1
+3.3V: C39.1, C40.1, C48.1, C49.1, C58.1, C59.1, C82.1, C83.1, C84.1, C85.1, C90.1, D17.2 (A), J3.4 (VDD), L7.2, R29.1, R63.1, TP14.1, U18.17 (VDD), U18.30 (VDD), U18.39 (VDD), U18.52 (VDD), U18.62 (VDD), U18.72 (VDD), U18.84 (VDD), U18.108 (VDD), U18.121 (VDD), U18.131 (VDD), U18.144 (VDD), U21.1 (EN), U21.4 (VIN), U25.21 (VCC)
+3.3VA: C3.1, C88.1, C89.1, U18.32 (VREF+), U18.33 (VDDA)
+BATT: BT1.1 (+), U18.6 (VBAT)
/BOOT0: R22.1, U18.138 (BOOT0)
/Keypad/SW_COL1: D1.1 (K), D5.1 (K), D9.1 (K), D13.1 (K), U25.10 (COL1)
/Keypad/SW_COL2: D2.1 (K), D6.1 (K), D10.1 (K), D14.1 (K), U25.11 (COL2)
/Keypad/SW_COL3: D3.1 (K), D7.1 (K), D11.1 (K), D15.1 (K), U25.12 (COL3)
/Keypad/SW_COL4: D4.1 (K), D8.1 (K), D12.1 (K), D16.1 (K), U25.13 (COL4)
/Keypad/SW_ROW1: SW1.1, SW2.1, SW3.1, SW4.1, U25.7 (ROW1)
/Keypad/SW_ROW2: SW5.1, SW6.1, SW7.1, SW8.1, U25.6 (ROW2)
/Keypad/SW_ROW3: SW9.1, SW10.1, SW11.1, SW12.1, U25.5 (ROW3)
/Keypad/SW_ROW4: SW13.1, SW14.1, SW15.1, SW16.1, U25.4 (ROW4)
/Power/3v3_PG: R63.2, R72.1, R72.2, U20.6 (PG)
/SWD_RESET: C81.2, R64.2, U18.25 (NRST)
GND: C1.2, C2.2, C3.2, C39.2, C40.2, C41.2, C42.2, C49.2, C50.2, C58.2, C59.2, C81.1, C82.2, C83.2, C84.2, C85.2, C88.2, C89.2, C90.2, J2.A1 (GND), J2.A12 (GND), J2.B1 (GND), J2.B12 (GND), J2.S1 (SHIELD), J3.6 (VSS), J3.11 (SHIELD), R22.2, R54.2, R56.2, U2.3 (GND), U3.3 (GND), U4.3 (GND), U5.3 (GND), U6.3 (GND), U7.3 (GND), U8.3 (GND), U9.3 (GND), U10.3 (GND), U11.3 (GND), U12.3 (GND), U13.3 (GND), U14.3 (GND), U15.3 (GND), U16.3 (GND), U17.3 (GND), U18.16 (VSS), U18.31 (VSSA), U18.38 (VSS), U18.51 (VSS), U18.61 (VSS), U18.83 (VSS), U18.94 (VSS), U18.107 (VSS), U18.120 (VSS), U18.130 (VSS), U20.1 (GND), U21.2 (GND), U25.19 (GND), U25.25 (EP)
unnamed: C1.1, U18.106 (VCAP)
unnamed: C2.1, U18.71 (VCAP)
unnamed: D1.2 (A), SW1.2
unnamed: D2.2 (A), SW2.2
unnamed: D3.2 (A), SW3.2
unnamed: D4.2 (A), SW4.2
unnamed: D5.2 (A), SW5.2
unnamed: D6.2 (A), SW6.2
unnamed: D7.2 (A), SW7.2
unnamed: D8.2 (A), SW8.2
unnamed: D9.2 (A), SW9.2
unnamed: D10.2 (A), SW10.2
unnamed: D11.2 (A), SW11.2
unnamed: D12.2 (A), SW12.2
unnamed: D13.2 (A), SW13.2
unnamed: D14.2 (A), SW14.2
unnamed: D15.2 (A), SW15.2
unnamed: D16.2 (A), SW16.2
unnamed: U2.2 (DOUT), U3.4 (DIN)
unnamed: U3.2 (DOUT), U4.4 (DIN)
unnamed: U4.2 (DOUT), U5.4 (DIN)
unnamed: U5.2 (DOUT), U6.4 (DIN)
unnamed: U6.2 (DOUT), U7.4 (DIN)
unnamed: U7.2 (DOUT), U8.4 (DIN)
unnamed: U8.2 (DOUT), U9.4 (DIN)
unnamed: U9.2 (DOUT), U10.4 (DIN)
unnamed: U10.2 (DOUT), U12.4 (DIN)
unnamed: U11.4 (DIN), U13.2 (DOUT)
unnamed: U12.2 (DOUT), U14.4 (DIN)
unnamed: U13.4 (DIN), U15.2 (DOUT)
unnamed: U14.2 (DOUT), U16.4 (DIN)
unnamed: U15.4 (DIN), U17.2 (DOUT)
unnamed: U16.2 (DOUT), U17.4 (DIN)
unnamed: C48.2, R29.2, R54.1, U20.5 (FB)
unnamed: L7.1, U20.2 (SW)
unnamed: R55.2, R56.1, U21.5 (FB)
unnamed: L3.1, U21.3 (PH)
unnamed: U22.8 (GND), U22.15 (GND)
unnamed: U27.10 (CC1), U27.11 (CC1)
unnamed: U27.1 (CC2), U27.14 (CC2)
unnamed: U27.8 (GND), U27.9 (GND), U27.15 (GND)
unnamed: U27.3 (VDD), U27.4 (VDD)
VBUS: J2.A4 (VBUS), J2.A9 (VBUS), J2.B4 (VBUS), J2.B9 (VBUS)
VDD: C50.1, U1.4 (SW), U2.1 (VDD), U3.1 (VDD), U4.1 (VDD), U5.1 (VDD), U6.1 (VDD), U7.1 (VDD), U8.1 (VDD), U9.1 (VDD), U10.1 (VDD), U11.1 (VDD), U12.1 (VDD), U13.1 (VDD), U14.1 (VDD), U15.1 (VDD), U16.1 (VDD), U17.1 (VDD), U20.3 (VIN)

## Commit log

2025-08-08 feat: various layout adjustments
2025-08-08 feat: project organization, add knob, pcb layout, and 3d models
2025-08-08 feat: various scroll wheel layout changes
2025-08-09 feat: add various connectors
2025-08-09 feat: various footprint updates, 3d models, tollerances
2025-08-09 feat: audio schematic, FMC bus, SDRAM connections
2025-08-09 feat: start codec layout
2025-08-10 feat: various layouts, changed SDRAM to BGA
2025-08-10 chore: added .gitignore to knob project
2025-08-10 feat: BGA routing for SDRAM
2025-08-10 feat: more SDRAM routing
2025-08-10 feat: display FPC routing
2025-08-11 feat: various audio and power schematic layout
2025-08-11 feat: speaker amplifier setup
2025-08-11 feat: audio system layout
2025-08-12 feat: change codec to NAU88C22YG
2025-08-12 feat: add speaker
2025-08-12 feat: add speaker model to symbol
2025-08-12 feat: add MEMs microphone
2025-08-13 feat: various PCB layout and routing
2025-08-13 chore: display FPC layout
2025-08-13 chore: shift STM32 closer to FPC
2025-08-13 feat: add BMPU debug connector
2025-08-13 feat: add micro SD slot model
2025-08-13 feat: fit SD card and SPI bus to layout
2025-08-13 chore: audio routing and UART port mapping
2025-08-14 fix: disconnected net buses
2025-08-15 feat: add audio routing muxes
2025-08-15 chore: add some notes about sequencer goals to README.md
2025-08-16 feat: various layout, start adding capacitive pads
2025-08-16 feat: add integrated flash memory
2025-08-17 feat: add ESD filter
2025-08-17 feat: route NOR flash
2025-08-19 feat: start adding velocity button circuit
2025-08-19 feat: resistor divider matrix for resistive touch
2025-08-20 feat: keypad schematic organization
2025-08-20 feat: update board layout to include velocity matrix
2025-08-20 feat: add anti-ghosting resistors to resistive matrix
2025-08-21 feat: keypad schematic cleanup
2025-08-21 feat: power schematic cleanup, add USB PD controller
2025-08-21 feat: start adding battery fuel gauge
2025-08-21 feat: add buffer for LED logic level conversion
2025-08-23 chore: schematic organization
2025-08-23 feat: add plated mounting holes
2025-08-23 chore: fix link in README
2025-08-23 fix: switch resistive pads not connected
2025-08-23 feat: start routing keyswitch pads
2025-08-27 fix: add reset MCU alternate function labels
2025-08-27 feat: audio system routing
2025-08-28 feat: keypad routing and layout
2025-08-31 feat: various routing, footprint and schematic cleanup
2025-09-01 feat: fix incorrect HSE crystal
2025-09-01 feat: start replacing expansion port with bluetooth module
2025-09-01 feat: clean up footprints, route bluetooth module
2025-09-01 feat: add SWD connector, route bluetooth, route velocity matrix
2025-09-01 feat: start adding headphone jack connector
2025-09-01 feat: start JLC DRC validation
2025-09-03 feat: various layout and routing
2025-09-03 chore: add notes for next revision
2025-09-03 chore: move hardware files into versioned directory
